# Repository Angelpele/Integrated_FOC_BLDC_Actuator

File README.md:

# **Integrated FOC BLDC Actuator**
A portable, self-contained closed loop Field Oriented Controller (FOC) for Brushless DC (BLDC) motors built on the ESP32-S3 via a custom designed PCB.
This project focuses on the development of a robust FOC controller for BLDC motors to be integrated into future robotic systems, such as robotic arms or other kind of robots. The controller combines the advantages of different motor technologies, offering:
- The **speed** of a BLDC motor
- The **precision** of a stepper motor
- The **torque** provided by cycloidal gear reductions

---

<p align="center">
  <em>Both CAD and 3D printed preliminary models</em>
</p>

---

## **Features and Goals**
- **High Performance**: Closed-loop sinusoidal PWM (SPWM) field-oriented control for precise speed, position, and torque management.
- **Integrated Protection**: Reverse polarity protection (RPP), fault detection for overvoltage, overcurrent, DRV8302 hardware faults (NFAULT/NOCTW), magnetic encoder field anomalies and IMU fault.
- **Advanced Sensors**: Magnetic encoder (MT6701) for precise motor shaft angle, BMI270 IMU for 3D acceleration and gyroscope tracking, and NTC thermistor for temperature monitoring.
- **Modularity**: Designed for portability and adaptability across multiple robotic platforms. Independent sensor and driver classes with clean interfaces.
- **Multi-Task Architecture**: FreeRTOS task scheduler on dual cores with semaphore and mutex protected shared data and a hardware timer ISR for all the control loops.
- **CAN Bus Communication**: MCP2551 transceiver for daisy chain communication in robotic systems.
- **Power Bus Connection**: Dual XT30 connectors provide easy connection between different motors in the same bus.

---

## **Hardware**
### **Core Components**
- **Microcontroller**: ESP32-S3 WROOM (dual core, 240 MHz)
- **Motor Driver**: DRV8302 3 phase gate driver with integrated current sense amplifiers
- **Sensors**:
  - **MT6701 Magnetic Encoder**: SSI interface, 14 bit resolution (16384 counts/rev), diametrically magnetized rotor for absolute shaft angle
  - **BMI270 IMU**: 3 axis accelerometer and gyroscope via 3 wire SPI
  - **NTC Thermistor**: B=3380 K, real time board temperature monitoring with Steinhart Hart equation
  - **PVDD Voltage Divider**: Resistor divider on ADC2 for bus voltage monitoring
- **CAN Transceiver**: MCP2551 for multi motor communication at up to 1 Mbps

### **Protection Features**
- Reverse polarity protection with integrated MOSFET and parallel zener diode
- TVS protection against exterior ESD discharges
- Overvoltage detection on PVDD (configurable threshold) with immediate driver shutdown
- DRV8302 hardware fault latch (NFAULT + NOCTW) with software latch counter and hysteresis
- MT6701 magnetic field anomaly detection
- IMU wrong data detection
- Watchdog timer (WDT) subscription on all FreeRTOS tasks to catch runaway loops

---

<p align="center">
  <em>Soldered PCB V1</em>
</p>

---

## **Mechanical Design**
- **Cycloidal Gearbox**: For torque amplification and precision gain, 15:1 gear reduction. Features dual disc configuration to supress motor vibrations.
- **Modified motor coupling**: The motor and gearbox coupler presents a D slot to transfer the rotation power without the need for small screws as in previous versions.
- **Integrated bearings**: Metallic bearings offer a smooth movement of the gearbox with outer steel pins.
- **Integrated Motor**: 5010 750KV motor integrated into the enclosure.
- **Integrated PCB**: The PCB support has been designed to be as compact as possible, reading the magnet from the motor axis and preventing external cables outside the casing.
- **Custom PCB (V1)**: Compact integration of ESP32-S3, DRV8302, MT6701, BMI270, MCP2551, and NTC. Schematic available in `ESP32_Motor_Controller_V1.pdf`.
- **Custom PCB (V2)**: Several improvements implemented and corrected errors from V1:
  - Voltage upgrade: Input raised to 36 V (MOSFET max 40 V); RPP, TVS diode, phase voltage dividers, and MOSFET selection updated accordingly (targeting ≥50 V rating).
  - Dual configuration for higher power motors and lower power ones (16V vs 36V).
  - Passives:
    - Large-value caps (22 µF, 1 µF) moved to 0805+ for voltage headroom
    - All MOSFET line power caps in 0805
    - GVDD/AVDD/DVDD decoupling can stay 0603 (16 V rated)
    - BOM consolidated to reuse values/footprints.
  - Layout:
    - Power and sensor zones separated
    - Routing improved with stitching vias
    - External pull-up resistors added on I2C lines
  - Gate series resistance tuned.
  - Schematic available in `ESP32_Motor_Controller_V2.pdf`.

---

<p align="center">
  <em>Mechanical CAD Design</em>
</p>

---

## **Firmware Architecture**

### **State Machine**
The main task runs a three-state machine:

```
SYSTEM_INIT → SYSTEM_CALIBRATION → SYSTEM_RUNNING
```

- **INIT**: Initializes MT6701 and DRV8302. Retries on failure.
- **CALIBRATION**: Sets up MCPWM, performs current sense offset calibration (DC_CAL pulse, 500 samples averaged), and magnetic encoder field quality check (1000 samples).
- **RUNNING**: Monitors faults in the main loop; all control logic runs in ISR-driven FreeRTOS tasks.

### **Control Loop (Timer ISR at 20 kHz)**
A hardware timer (APB clock / 80 divider = 1 MHz, alarm at 50 µs) triggers task notifications at divided rates:

| Task | Rate | Core | Priority |
|---|---|---|---|
| `focLoop` | 20 kHz | 1 | 10 |
| `magLoop` | 5 kHz | 1 | 9 |
| `drvLoop` | 500 Hz | 0 | 8 |
| `telemetryLoop` | 100 Hz | 0 | 2 |

All shared data (`drv_pkg`, `mag_pkg`) is protected by FreeRTOS mutexes.

### **SPWM Generation**
`DRV::update_spwm()` runs three stages:

1. **Alignment (Open loop)**: Ramps duty cycle over 500 ms to lock rotor to a known electrical angle. Computes `elec_offset` from the MT6701 reading at alignment.
2. **Frequency Ramp**: Linearly ramps `electrical_freq` from 2 Hz to `target_electrical_freq` (20 Hz default) at 100 Hz/s.
3. **Closed Loop SPWM**: Uses MT6701 angle + `elec_offset` + pole pairs (7) to compute instantaneous electrical angle.

Motor parameters (5010 750KV, 14 poles, 270 mΩ phase resistance, 40 A max) are defined as `constexpr` in `DRV.h`.

### **Current Sensing**
- Two shunt channels (SO1, SO2) on ADC1 with DRV8302 internal amplifier (gain selectable via GAIN pin, default 40×, R_shunt = 10 mΩ)
- DC offset calibration via `DC_CAL` pin pulse at startup, sanity-checked against 12-bit midpoint (valid range 1000–3000)
- Third phase current reconstructed as `I_C = -(I_A + I_B)`

---

## **Software**
1. **Motor Calibration**: Automated at boot — current sense offset calibration and magnetic field quality verification.
2. **Real Time Telemetry**: UART serial output at 100 Hz: PVDD voltage, phase currents, raw ADC values, NFAULT/NOCTW states, NTC temperature, and encoder angle/status.
3. **Debug Mode**: `debug_mode_enabled` flag bypasses the state machine for rapid hardware-in-the-loop testing.
4. **Fault Override**: Per-subsystem override flags (`DRV::set_override`, `MT6701::set_override`) for bench testing without a valid magnetic field or full power stage.

Integration with ROS2 and a graphical PID tuning interface are planned for future iterations.

---

## **References**
- [SimpleFOC Library](https://github.com/simplefoc/simplefoc)
- [ODrive Pro Documentation](https://docs.odriverobotics.com/v/latest/hardware/pro-datasheet.html)
- DRV8302 Datasheet (`drv8302.pdf`)
- MT6701 SSI Encoder Datasheet
- ESP32-S3 WROOM Datasheet (`ESp32_S3_WROOM.pdf`)

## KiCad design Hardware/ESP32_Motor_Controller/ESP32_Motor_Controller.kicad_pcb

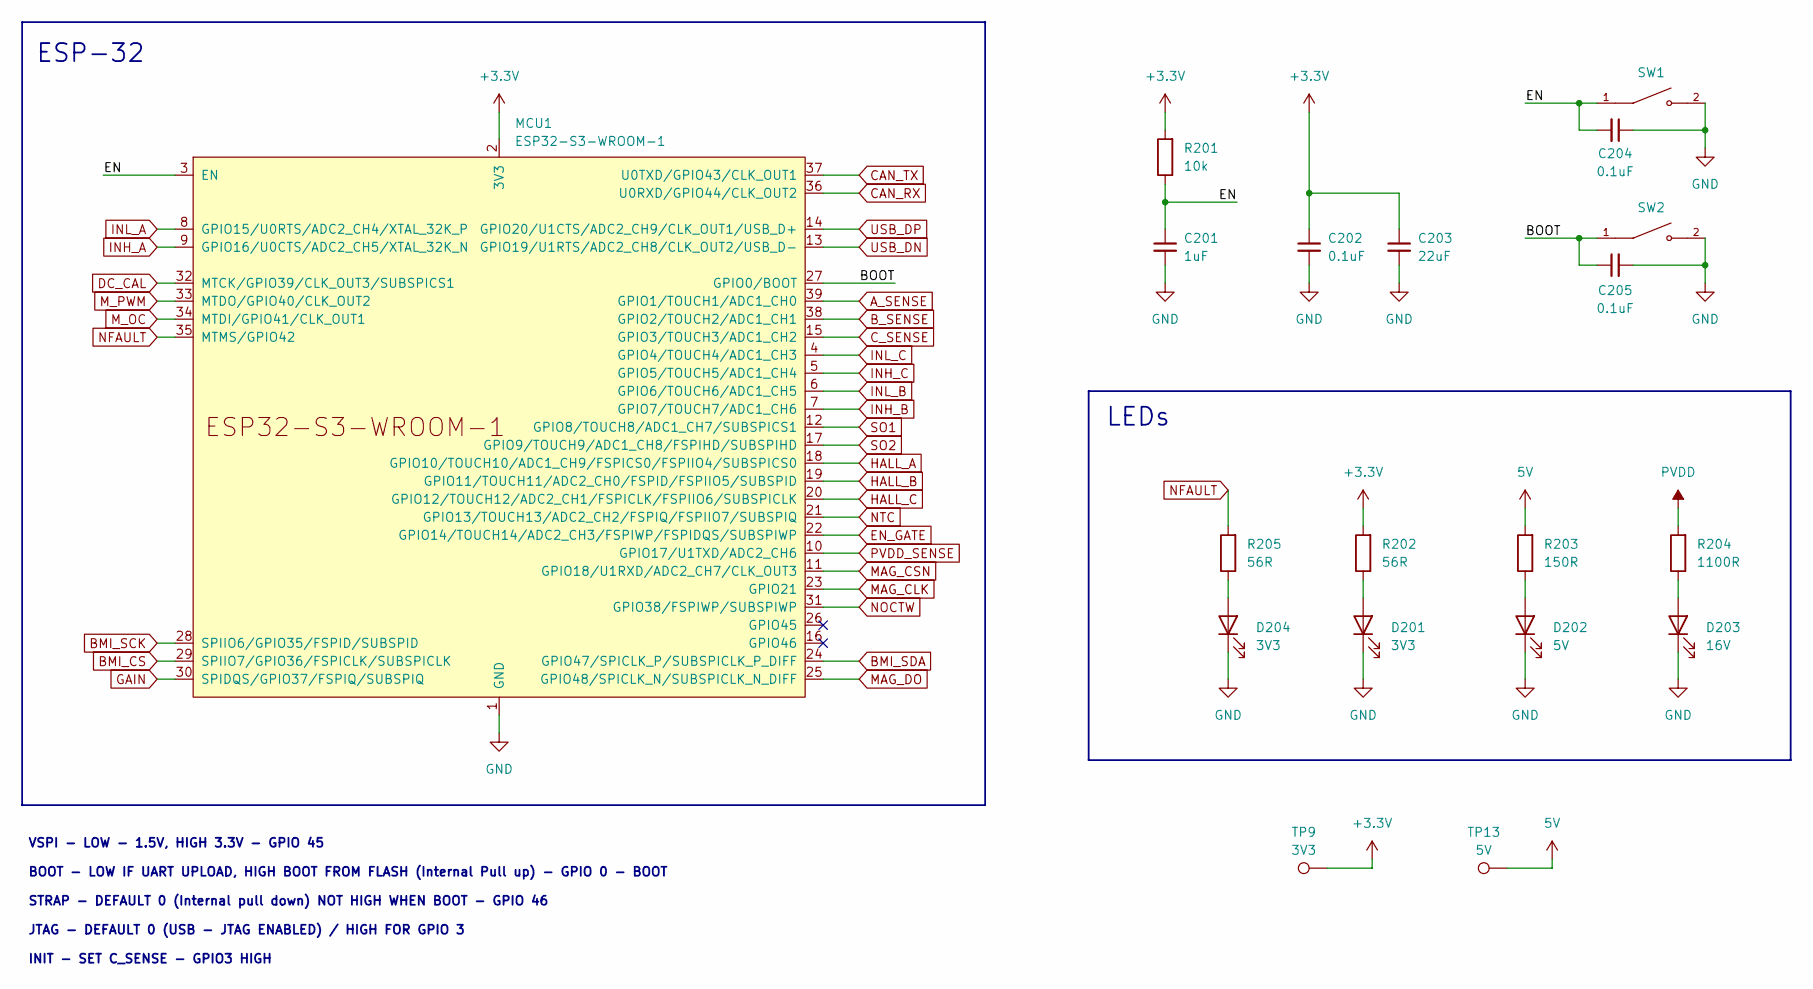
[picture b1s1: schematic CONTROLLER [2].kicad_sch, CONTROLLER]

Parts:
C201: 1uF; C_0603_1608Metric
C202, C204, C205: 0.1uF; C_0402_1005Metric
C203: 22uF; C_0805_2012Metric
D201, D204: 3V3; LED_0603_1608Metric
D202: 5V; LED_0603_1608Metric
D203: 16V; LED_0603_1608Metric
MCU1: ESP32-S3-WROOM-1; ESP32-S3-WROOM-1U
R201: 10k; R_0402_1005Metric
R202, R205: 56R; R_0603_1608Metric
R203: 150R; R_0603_1608Metric
R204: 1100R; R_0603_1608Metric
SW1, SW2: TS-1088-AR02016; SW_TS-1088-AR02016; PARTREV N/A
TP9: 3V3; TestPoint_Pad_D1.0mm
TP13: 5V; TestPoint_Pad_D1.0mm

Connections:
3V3: C202.1, C203.1, MCU1.2 (3V3), R201.2, R202.2, TP9.1; also elsewhere on the board
5V: R203.2, TP13.1; also elsewhere on the board
/CONTROLLER/BOOT: C205.1, MCU1.27 (GPIO0/BOOT), SW2.1; also elsewhere on the board
/CONTROLLER/EN: C201.1, C204.2, MCU1.3 (EN), R201.1, SW1.1; also elsewhere on the board
AGND: C201.2, C202.2, C203.2, C204.1, C205.2, D201.1 (K), D202.1 (K), D203.1 (K), D204.1 (K), MCU1.1 (GND), MCU1.40 (GND), MCU1.41 (GND), SW1.2, SW2.2; also elsewhere on the board
NFAULT: MCU1.35 (MTMS/GPIO42), R205.2; also elsewhere on the board
unnamed: D201.2 (A), R202.1
unnamed: D202.2 (A), R203.1
unnamed: D203.2 (A), R204.1
unnamed: D204.2 (A), R205.1
PVDD: R204.2; also elsewhere on the board

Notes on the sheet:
VSPI - LOW - 1.5V, HIGH 3.3V - GPIO 45 BOOT - LOW IF UART UPLOAD, HIGH BOOT FROM FLASH (Internal Pull up) - GPIO 0 - BOOT STRAP - DEFAULT 0 (Internal pull down) NOT HIGH WHEN BOOT - GPIO 46 JTAG - DEFAULT 0 (USB - JTAG ENABLED) / HIGH FOR GPIO 3 INIT - SET C_SENSE - GPIO3 HIGH
ESP-32
LEDs

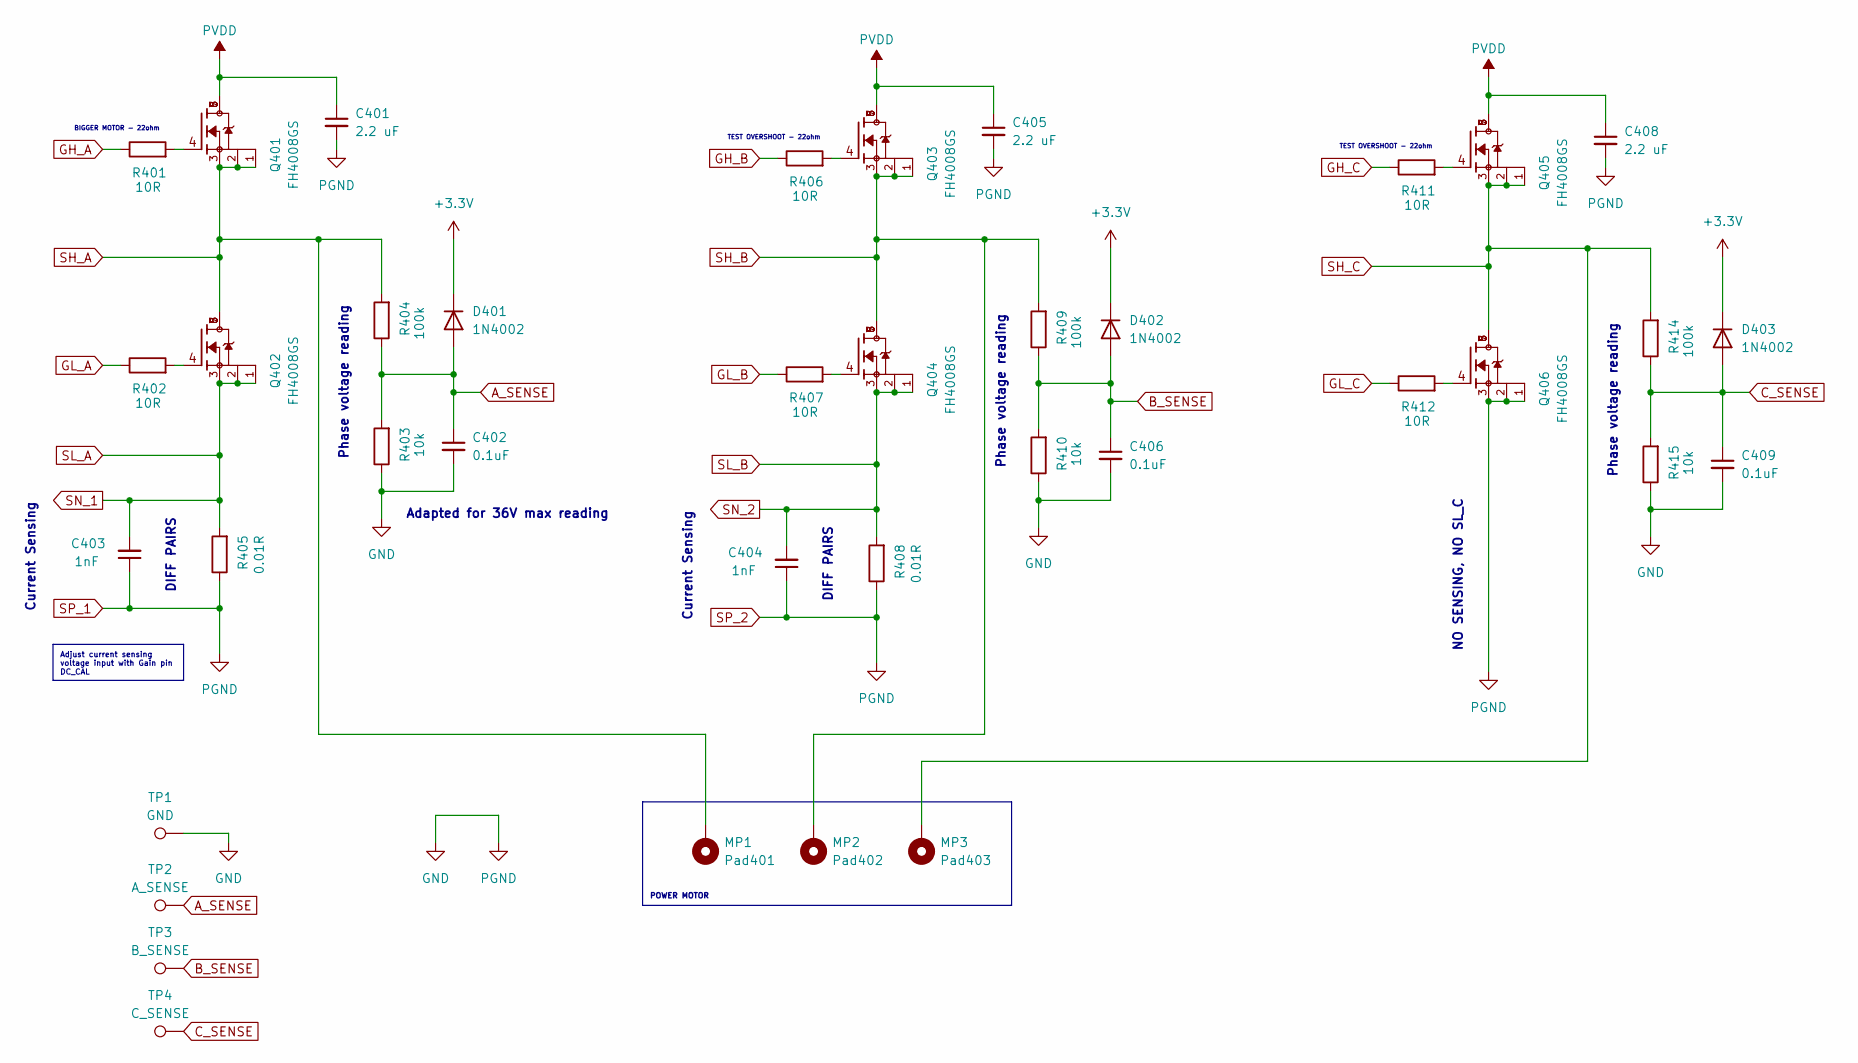
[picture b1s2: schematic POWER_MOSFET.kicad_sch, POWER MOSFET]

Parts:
C401, C405, C408: 2.2 uF; C_0805_2012Metric
C402, C406, C409: 0.1uF; C_0402_1005Metric
C403, C404: 1nF; C_0402_1005Metric
D401, D402, D403: 1N4002; D_SOD-123
MP1: Pad401; MountingHole_2.5mm_Pad_Via
MP2: Pad402; MountingHole_2.5mm_Pad_Via
MP3: Pad403; MountingHole_2.5mm_Pad_Via
Q401, Q402, Q403, Q404, Q405, Q406: FH4008GS; PQFN-8-EP_6x5mm_P1.27mm_Generic
R401, R402, R406, R407, R411, R412: 10R; R_0603_1608Metric
R403, R410, R415: 10k; R_0402_1005Metric
R404, R409, R414: 100k; R_0402_1005Metric
R405, R408: 0.01R; R_2512_6332Metric
TP1: GND; TestPoint_Pad_D1.0mm
TP2: A_SENSE; TestPoint_Pad_D1.0mm
TP3: B_SENSE; TestPoint_Pad_D1.0mm
TP4: C_SENSE; TestPoint_Pad_D1.0mm

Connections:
3V3: D401.1 (K), D402.1 (K), D403.1 (K); also elsewhere on the board
AGND: C401.2, C402.2, C403.1, C404.1, C405.2, C406.2, C408.2, C409.2, Q406.1, Q406.2, Q406.3, R403.1, R405.1, R408.1, R410.1, R415.1, TP1.1; also elsewhere on the board
A_SENSE: C402.1, D401.2 (A), R403.2, R404.1, TP2.1; also elsewhere on the board
B_SENSE: C406.1, D402.2 (A), R409.1, R410.2, TP3.1; also elsewhere on the board
C_SENSE: C409.1, D403.2 (A), R414.1, R415.2, TP4.1; also elsewhere on the board
GH_A: R401.1; also elsewhere on the board
GH_B: R406.1; also elsewhere on the board
GH_C: R411.1; also elsewhere on the board
GL_A: R402.1; also elsewhere on the board
GL_B: R407.1; also elsewhere on the board
GL_C: R412.1; also elsewhere on the board
unnamed: Q401.4, R401.2
unnamed: Q402.4, R402.2
unnamed: Q403.4, R406.2
unnamed: Q404.4, R407.2
unnamed: Q405.4, R411.2
unnamed: Q406.4, R412.2
PVDD: C401.1, C405.1, C408.1, Q401.5, Q401.6, Q401.7, Q401.8, Q403.5, Q403.6, Q403.7, Q403.8, Q405.5, Q405.6, Q405.7, Q405.8; also elsewhere on the board
SH_A: MP1.1, Q401.1, Q401.2, Q401.3, Q402.5, Q402.6, Q402.7, Q402.8, R404.2; also elsewhere on the board
SH_B: MP2.1, Q403.1, Q403.2, Q403.3, Q404.5, Q404.6, Q404.7, Q404.8, R409.2; also elsewhere on the board
SH_C: MP3.1, Q405.1, Q405.2, Q405.3, Q406.5, Q406.6, Q406.7, Q406.8, R414.2; also elsewhere on the board
SL_A: C403.2, Q402.1, Q402.2, Q402.3, R405.2; also elsewhere on the board
SL_B: C404.2, Q404.1, Q404.2, Q404.3, R408.2; also elsewhere on the board

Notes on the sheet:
NO SENSING, NO SL_C
Current Sensing
TEST OVERSHOOT - 22ohm
BIGGER MOTOR - 22ohm
Adapted for 36V max reading
Phase voltage reading
DIFF PAIRS
POWER MOTOR
Adjust current sensing voltage input with Gain pin DC_CAL

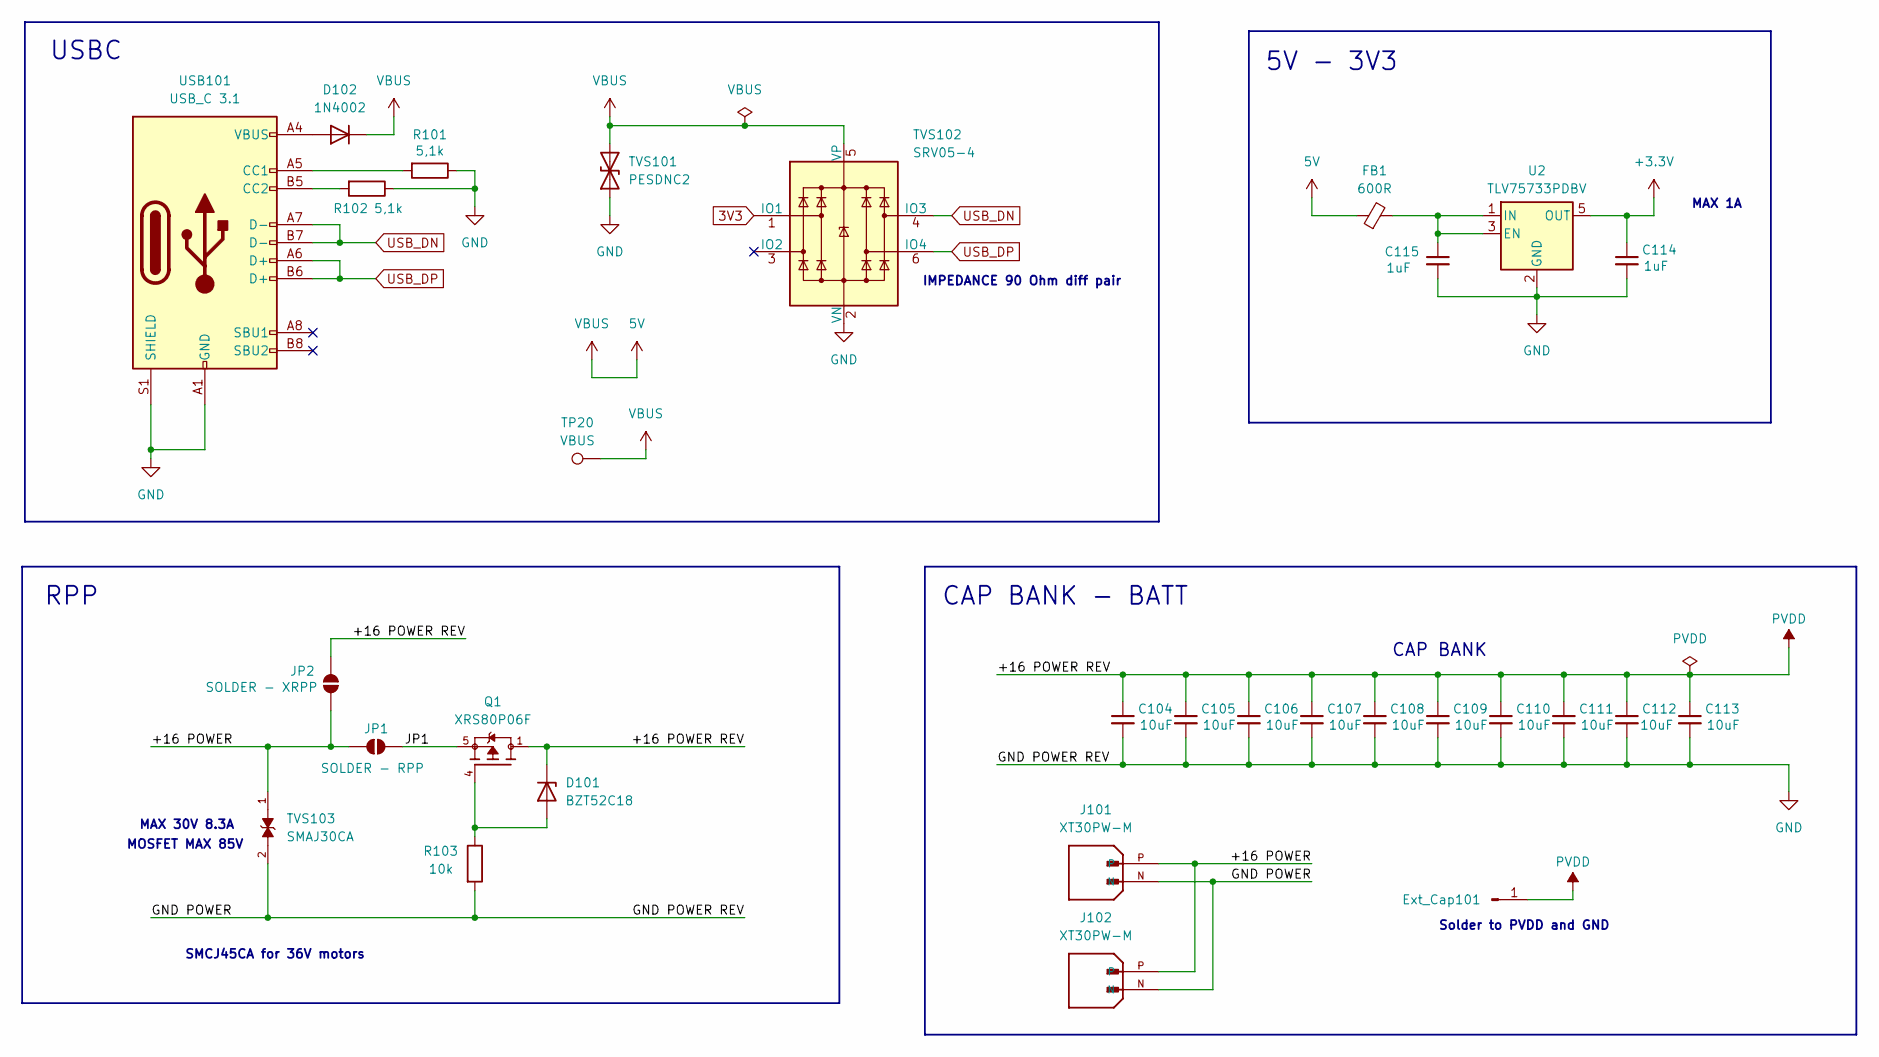
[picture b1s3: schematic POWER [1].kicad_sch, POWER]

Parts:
C104, C105, C106, C107, C108, C109, C110, C111, C112, C113: 10uF; C_0805_2012Metric
C114, C115: 1uF; C_0603_1608Metric
D101: BZT52C18; D_SOD-123
D102: 1N4002; D_SOD-123
Ext_Cap101: Conn_01x01_Pin; PinHeader_1x01_P2.00mm_Vertical
FB1: 600R; L_0603_1608Metric
J101, J102: XT30PW-M; AMASS_XT30PW-M; PARTREV 1.2
JP1: SOLDER - RPP; SolderJumper-2_P1.3mm_Open_Pad1.0x1.5mm
JP2: SOLDER - XRPP; SolderJumper-2_P1.3mm_Open_Pad1.0x1.5mm
Q1: XRS80P06F; MOUSER_PART_NUMBER 781-SI7149DP-GE3
R101, R102: 5,1k; R_0402_1005Metric
R103: 10k; R_0402_1005Metric
TP20: VBUS; TestPoint_Pad_D1.0mm
TVS101: PESDNC2; D_0201_0603Metric
TVS102: SRV05-4; SOT-23-6
TVS103: SMAJ30CA; D_SMC; PARTREV S2102; DigiKey_Part_Number 1801-SMAJ30CATR-ND
U2: TLV75733PDBV; SOT-23-5
USB101: USB_C 3.1; USB_C_Receptacle_Palconn_UTC16-G

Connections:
3V3: C114.1, TVS102.1 (IO1), U2.5 (OUT); also elsewhere on the board
5V: D102.1 (K), FB1.1, TP20.1, TVS101.2 (A2), TVS102.5 (VP); also elsewhere on the board
/POWER/+16 POWER: J101.P, J102.P, JP1.2 (B), JP2.1 (A), TVS103.1
/POWER/JP1: JP1.1 (A), Q1.5, Q1.6, Q1.7, Q1.8, Q1.9
AGND: C104.2, C105.2, C106.2, C107.2, C108.2, C109.2, C110.2, C111.2, C112.2, C113.2, C114.2, C115.2, J101.N, J102.N, R101.1, R102.1, R103.2, TVS101.1 (A1), TVS102.2 (VN), TVS103.2, U2.2 (GND), USB101.A1 (GND), USB101.A12 (GND), USB101.B1 (GND), USB101.B12 (GND), USB101.S1 (SHIELD); also elsewhere on the board
unnamed: D101.2 (A), Q1.4, R103.1
unnamed 50: D102.2 (A), USB101.A4 (VBUS), USB101.A9 (VBUS), USB101.B4 (VBUS), USB101.B9 (VBUS); also elsewhere on the board
unnamed 66: C115.1, FB1.2, U2.1 (IN), U2.3 (EN); also elsewhere on the board
unnamed 83: R101.2, USB101.A5 (CC1); also elsewhere on the board
unnamed 84: R102.2, USB101.B5 (CC2); also elsewhere on the board
PVDD: C104.1, C105.1, C106.1, C107.1, C108.1, C109.1, C110.1, C111.1, C112.1, C113.1, D101.1 (K), Ext_Cap101.1, JP2.2 (B), Q1.1, Q1.2, Q1.3; also elsewhere on the board
USB_DN: TVS102.4 (IO3), USB101.A7 (D-), USB101.B7 (D-); also elsewhere on the board
USB_DP: TVS102.6 (IO4), USB101.A6 (D+), USB101.B6 (D+); also elsewhere on the board

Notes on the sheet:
RPP
MAX 30V 8.3A
Solder to PVDD and GND
5V - 3V3
USBC
MAX 1A
SMCJ45CA for 36V motors
IMPEDANCE 90 Ohm diff pair
MOSFET MAX 85V
CAP BANK - BATT
CAP BANK

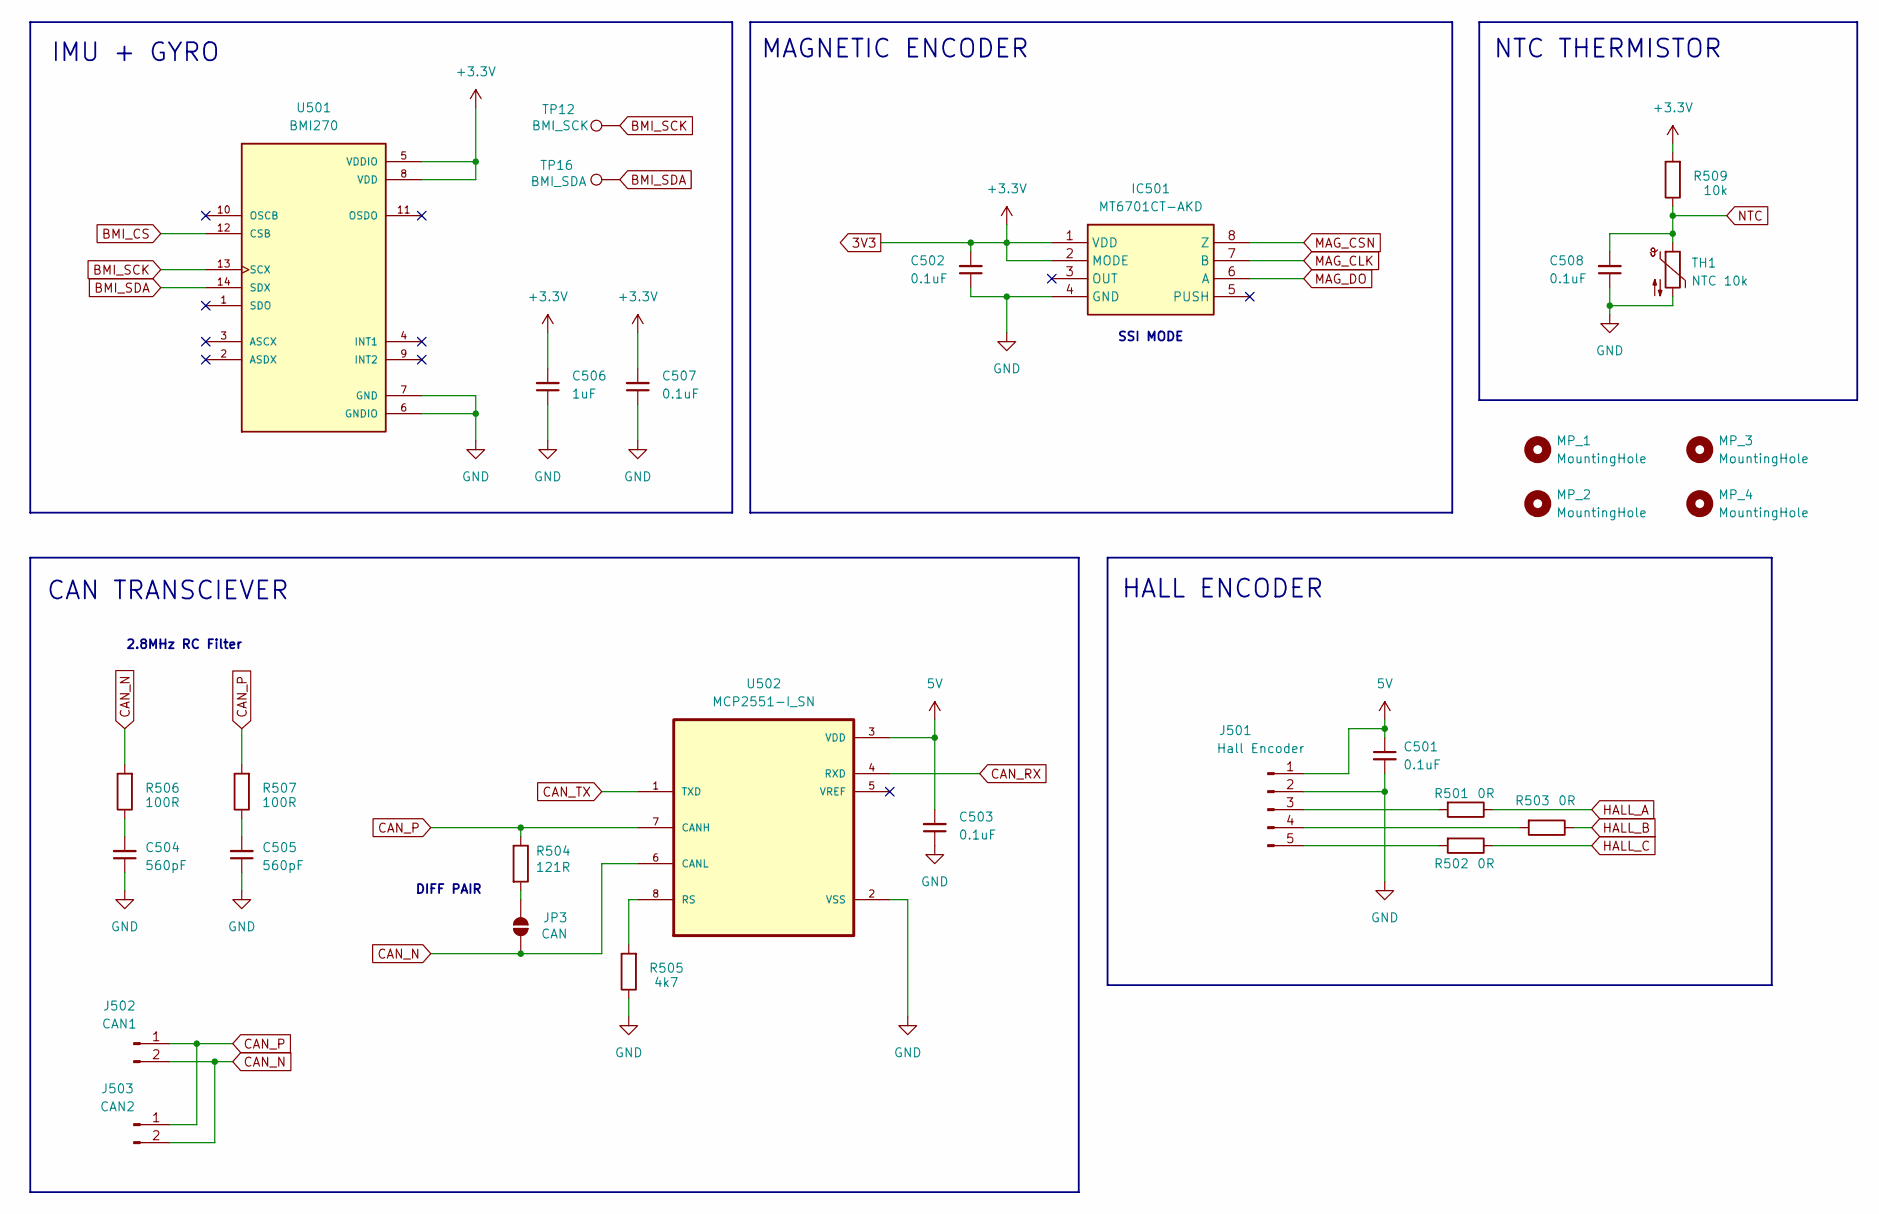
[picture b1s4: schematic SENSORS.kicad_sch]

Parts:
C501, C502, C503, C507, C508: 0.1uF; C_0402_1005Metric
C504, C505: 560pF; R_0402_1005Metric
C506: 1uF; C_0402_1005Metric
IC501: MT6701CT-AKD; SOIC127P600X175-8N; Manufacturer_Part_Number MT6701CT-STD-R
J501: Hall Encoder; JST_PH_S5B-PH-K_1x05_P2.00mm_Horizontal
J502: CAN1; JST_PH_S2B-PH-K_1x02_P2.00mm_Horizontal
J503: CAN2; JST_PH_S2B-PH-K_1x02_P2.00mm_Horizontal
JP3: CAN; SolderJumper-2_P1.3mm_Open_Pad1.0x1.5mm
MP_1, MP_2, MP_3, MP_4: MountingHole; MountingHole_3.2mm_M3
R501, R502, R503: 0R; R_0402_1005Metric
R504: 121R; R_0603_1608Metric
R505: 4k7; R_0402_1005Metric
R506, R507: 100R; R_0603_1608Metric
R509: 10k; R_0402_1005Metric
TH1: NTC 10k; R_0603_1608Metric
TP12: BMI_SCK; TestPoint_Pad_D1.0mm
TP16: BMI_SDA; TestPoint_Pad_D1.0mm
U501: BMI270; XDCR_BMI270
U502: MCP2551-I_SN; SOIC127P599X175-8N

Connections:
3V3: C502.2, C506.2, C507.2, IC501.1 (VDD), IC501.2 (MODE), R509.2, U501.5 (VDDIO), U501.8 (VDD); also elsewhere on the board
5V: C501.1, C503.2, J501.1, U502.3 (VDD); also elsewhere on the board
AGND: C501.2, C502.1, C503.1, C504.1, C505.1, C506.1, C507.1, C508.1, IC501.4 (GND), J501.2, R505.1, TH1.2, U501.6 (GNDIO), U501.7 (GND), U502.2 (VSS); also elsewhere on the board
BMI_CS: U501.12 (CSB); also elsewhere on the board
BMI_SCK: TP12.1, U501.13 (SCX); also elsewhere on the board
BMI_SDA: TP16.1, U501.14 (SDX); also elsewhere on the board
CAN_N: J502.2, J503.2, JP3.1 (A), R506.2, U502.6 (CANL)
CAN_P: J502.1, J503.1, R504.1, R507.2, U502.7 (CANH)
CAN_RX: U502.4 (RXD); also elsewhere on the board
CAN_TX: U502.1 (TXD); also elsewhere on the board
HALL_A: R501.1; also elsewhere on the board
HALL_B: R503.1; also elsewhere on the board
HALL_C: R502.1; also elsewhere on the board
MAG_CLK: IC501.7 (B); also elsewhere on the board
MAG_CSN: IC501.8 (Z); also elsewhere on the board
MAG_DO: IC501.6 (A); also elsewhere on the board
NTC: C508.2, R509.1, TH1.1; also elsewhere on the board
unnamed: C504.2, R506.1
unnamed: C505.2, R507.1
unnamed: J501.3, R501.2
unnamed: J501.4, R503.2
unnamed: J501.5, R502.2
unnamed: JP3.2 (B), R504.2
unnamed: R505.2, U502.8 (RS)

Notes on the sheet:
IMU + GYRO
CAN TRANSCIEVER
2.8MHz RC Filter
DIFF PAIR
MAGNETIC ENCODER
HALL ENCODER
SSI MODE
NTC THERMISTOR

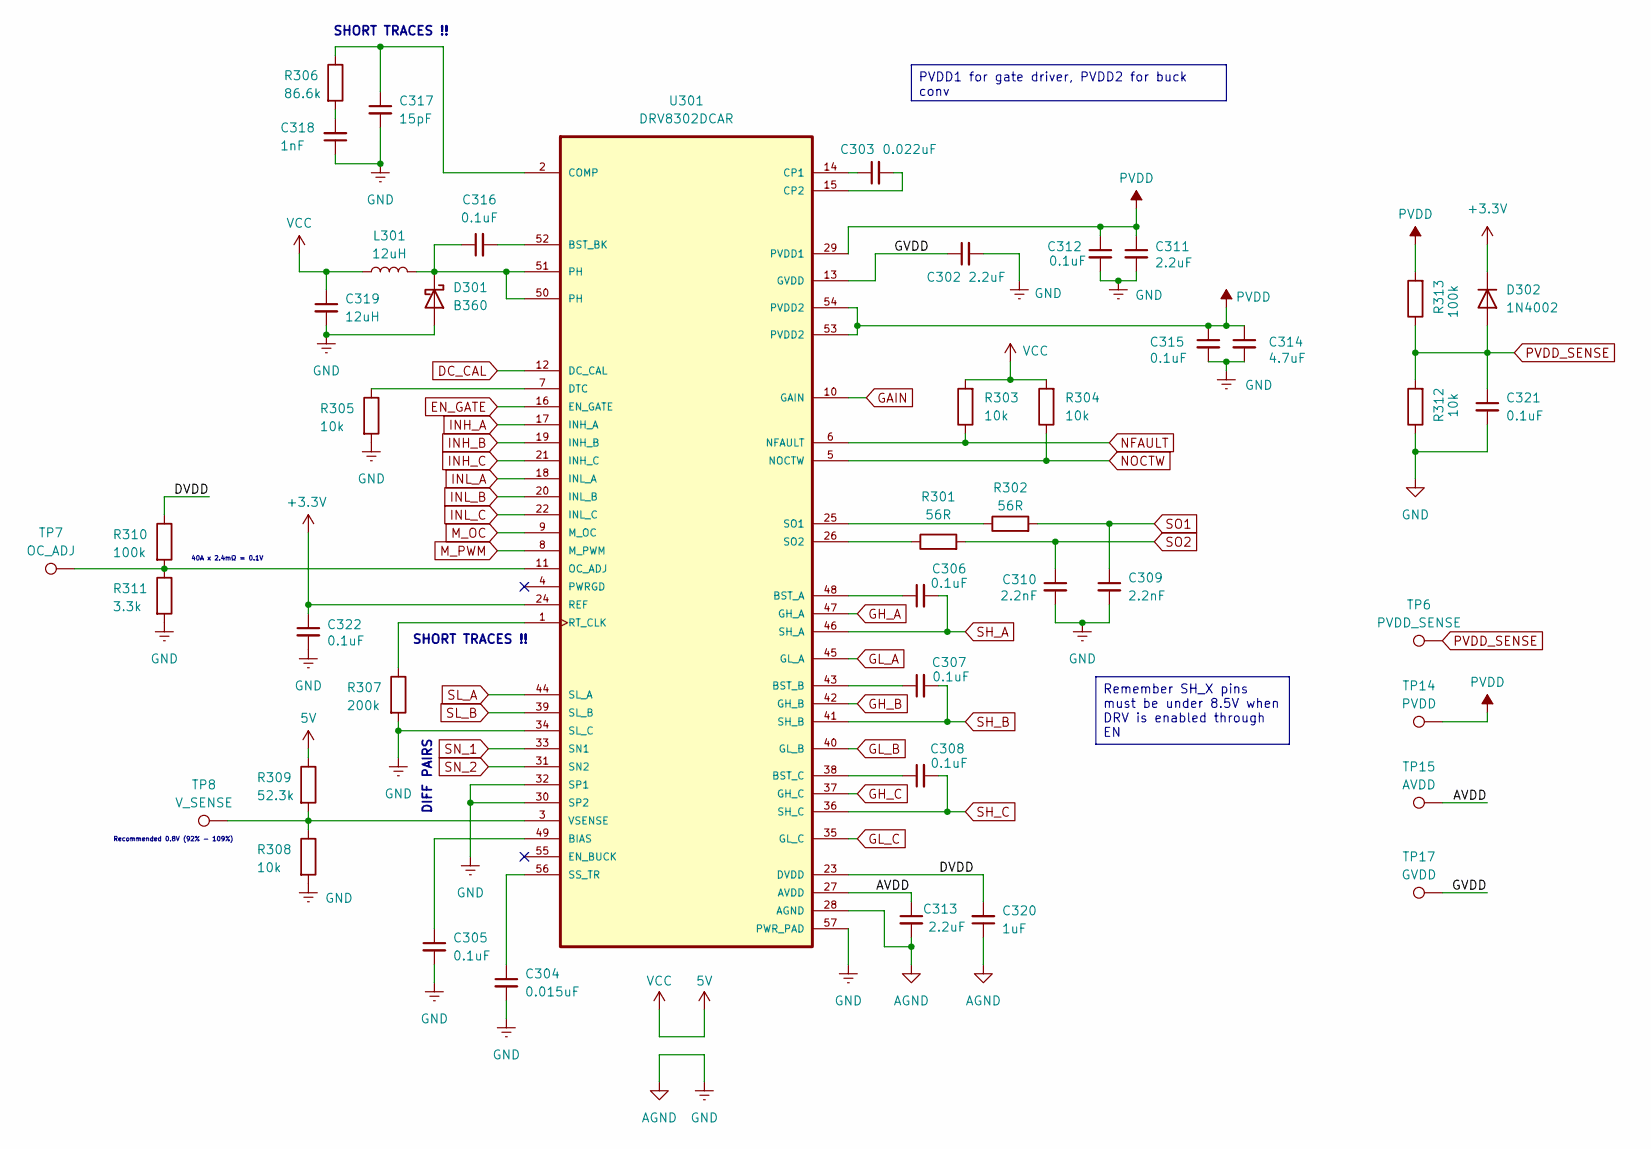
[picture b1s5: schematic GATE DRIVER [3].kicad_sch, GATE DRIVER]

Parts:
C302: 2.2uF; C_0603_1608Metric
C303: 0.022uF; C_0402_1005Metric
C304: 0.015uF; C_0402_1005Metric
C305, C322: 0.1uF; C_0402_1005Metric
C306, C307, C308, C321: 0.1uF; C_0603_1608Metric
C309, C310: 2.2nF; C_0402_1005Metric
C311, C313: 2.2uF; C_0805_2012Metric
C312, C315, C316: 0.1uF; C_0805_2012Metric
C314: 4.7uF; C_0805_2012Metric
C317: 15pF; C_0603_1608Metric
C318: 1nF; C_0402_1005Metric
C319: 12uH; C_0805_2012Metric
C320: 1uF; C_0603_1608Metric
D301: B360; B3030A
D302: 1N4002; D_SOD-123
L301: 12uH; SM7850
R301, R302: 56R; R_0402_1005Metric
R303, R304, R305: 10k; R_0402_1005Metric
R306: 86.6k; R_0402_1005Metric
R307: 200k; R_0402_1005Metric
R308, R312: 10k; R_0603_1608Metric
R309: 52.3k; R_0603_1608Metric
R310: 100k; R_0402_1005Metric
R311: 3.3k; R_0402_1005Metric
R313: 100k; R_0603_1608Metric
TP6: PVDD_SENSE; TestPoint_Pad_D1.0mm
TP7: OC_ADJ; TestPoint_Pad_D1mm
TP8: V_SENSE; TestPoint_Pad_D1.0mm
TP14: PVDD; TestPoint_Pad_D1.0mm
TP15: AVDD; TestPoint_Pad_D1.0mm
TP17: GVDD; TestPoint_Pad_D1.0mm
U301: DRV8302DCAR; DRV8302

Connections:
3V3: C322.1, D302.1 (K), U301.24 (REF); also elsewhere on the board
5V: C319.1, L301.1, R303.2, R304.2, R309.1; also elsewhere on the board
/GATE DRIVER/AVDD: C313.1, TP15.1, U301.27 (AVDD); also elsewhere on the board
/GATE DRIVER/DVDD: C320.2, R310.1, U301.23 (DVDD)
/GATE DRIVER/GVDD: C302.1, TP17.1, U301.13 (GVDD)
AGND: C302.2, C304.2, C305.2, C309.2, C310.2, C311.2, C312.2, C313.2, C314.2, C315.2, C317.2, C318.1, C319.2, C320.1, C321.2, C322.2, D301.2 (A), R305.2, R307.2, R308.2, R311.2, R312.1, U301.28 (AGND), U301.30 (SP2), U301.32 (SP1), U301.34 (SL_C), U301.57 (PWR_PAD); also elsewhere on the board
DC_CAL: U301.12 (DC_CAL); also elsewhere on the board
EN_GATE: U301.16 (EN_GATE); also elsewhere on the board
GAIN: U301.10 (GAIN); also elsewhere on the board
GH_A: U301.47 (GH_A); also elsewhere on the board
GH_B: U301.42 (GH_B); also elsewhere on the board
GH_C: U301.37 (GH_C); also elsewhere on the board
GL_A: U301.45 (GL_A); also elsewhere on the board
GL_B: U301.40 (GL_B); also elsewhere on the board
GL_C: U301.35 (GL_C); also elsewhere on the board
INH_A: U301.17 (INH_A); also elsewhere on the board
INH_B: U301.19 (INH_B); also elsewhere on the board
INH_C: U301.21 (INH_C); also elsewhere on the board
INL_A: U301.18 (INL_A); also elsewhere on the board
INL_B: U301.20 (INL_B); also elsewhere on the board
INL_C: U301.22 (INL_C); also elsewhere on the board
M_OC: U301.9 (M_OC); also elsewhere on the board
M_PWM: U301.8 (M_PWM); also elsewhere on the board
NFAULT: R303.1, U301.6 (NFAULT); also elsewhere on the board
NOCTW: R304.1, U301.5 (NOCTW); also elsewhere on the board
unnamed: C318.2, R306.2
unnamed: C316.1, D301.1 (K), L301.2, U301.50 (PH), U301.51 (PH)
unnamed: C305.1, U301.49 (BIAS)
unnamed: C306.1, U301.48 (BST_A)
unnamed: C307.1, U301.43 (BST_B)
unnamed: C316.2, U301.52 (BST_BK)
unnamed: C308.1, U301.38 (BST_C)
unnamed: C317.1, R306.1, U301.2 (COMP)
unnamed: C303.1, U301.14 (CP1)
unnamed: C303.2, U301.15 (CP2)
unnamed: R305.1, U301.7 (DTC)
unnamed: R310.2, R311.1, TP7.1, U301.11 (OC_ADJ)
unnamed: R307.1, U301.1 (RT_CLK)
unnamed: R302.1, U301.25 (SO1)
unnamed: R301.1, U301.26 (SO2)
unnamed: C304.1, U301.56 (SS_TR)
unnamed: R308.1, R309.2, TP8.1, U301.3 (VSENSE)
PVDD: C311.1, C312.1, C314.1, C315.1, R313.2, TP14.1, U301.29 (PVDD1), U301.53 (PVDD2), U301.54 (PVDD2); also elsewhere on the board
PVDD_SENSE: C321.1, D302.2 (A), R312.2, R313.1, TP6.1; also elsewhere on the board
SH_A: C306.2, U301.46 (SH_A); also elsewhere on the board
SH_B: C307.2, U301.41 (SH_B); also elsewhere on the board
SH_C: C308.2, U301.36 (SH_C); also elsewhere on the board
SL_A: U301.33 (SN1), U301.44 (SL_A); also elsewhere on the board
SL_B: U301.31 (SN2), U301.39 (SL_B); also elsewhere on the board
SO1: C309.1, R302.2; also elsewhere on the board
SO2: C310.1, R301.2; also elsewhere on the board

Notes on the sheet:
SHORT TRACES !!
DIFF PAIRS
Recommended 0.8V (92% - 109%)
40A x 2.4mΩ = 0.1V
PVDD1 for gate driver, PVDD2 for buck conv
Remember SH_X pins must be under 8.5V when DRV is enabled through EN
